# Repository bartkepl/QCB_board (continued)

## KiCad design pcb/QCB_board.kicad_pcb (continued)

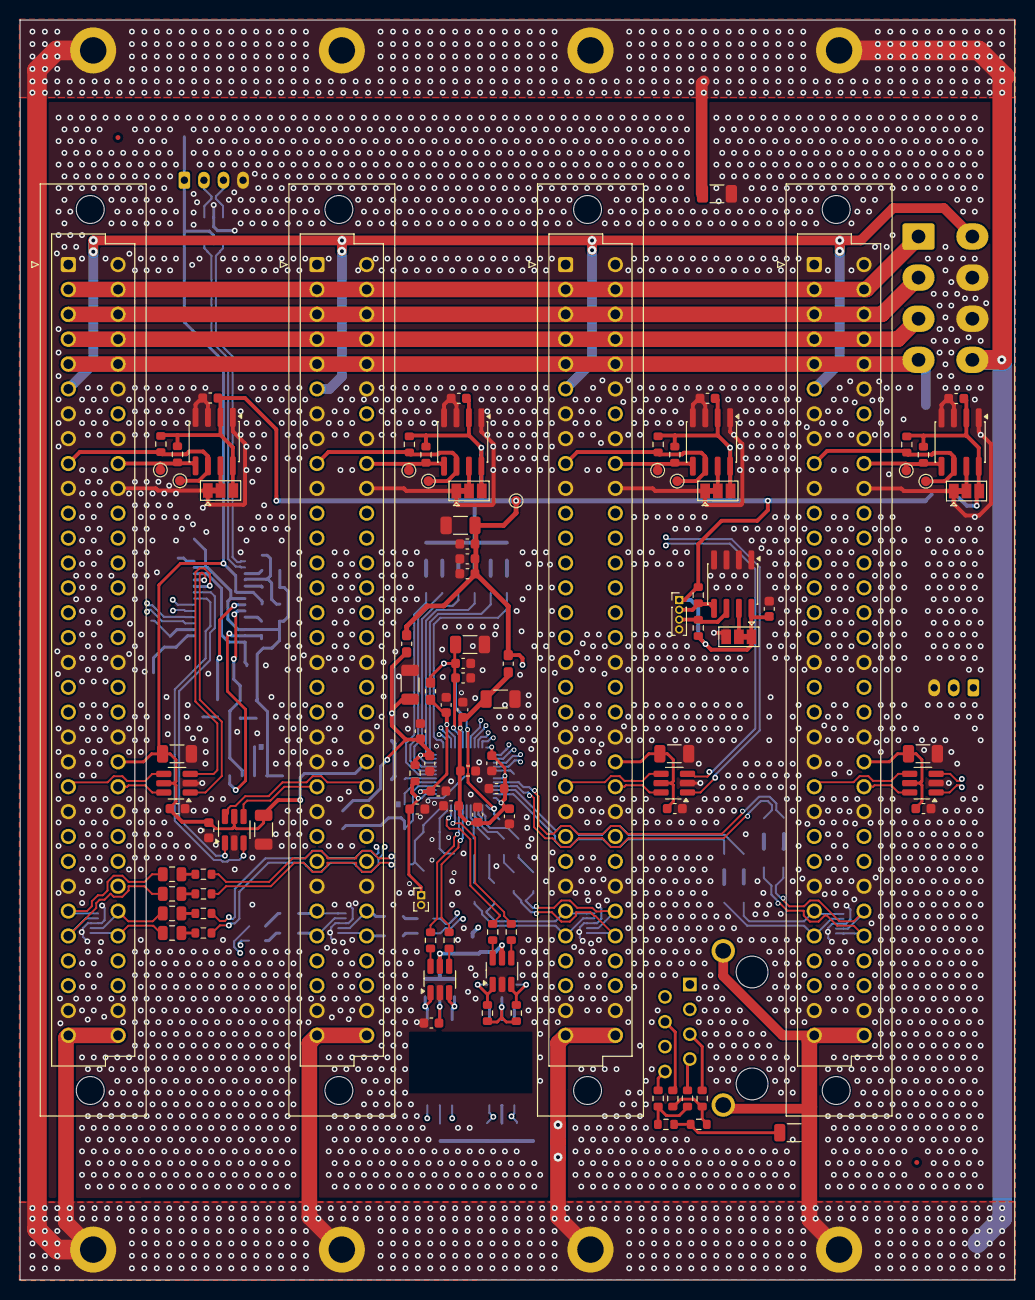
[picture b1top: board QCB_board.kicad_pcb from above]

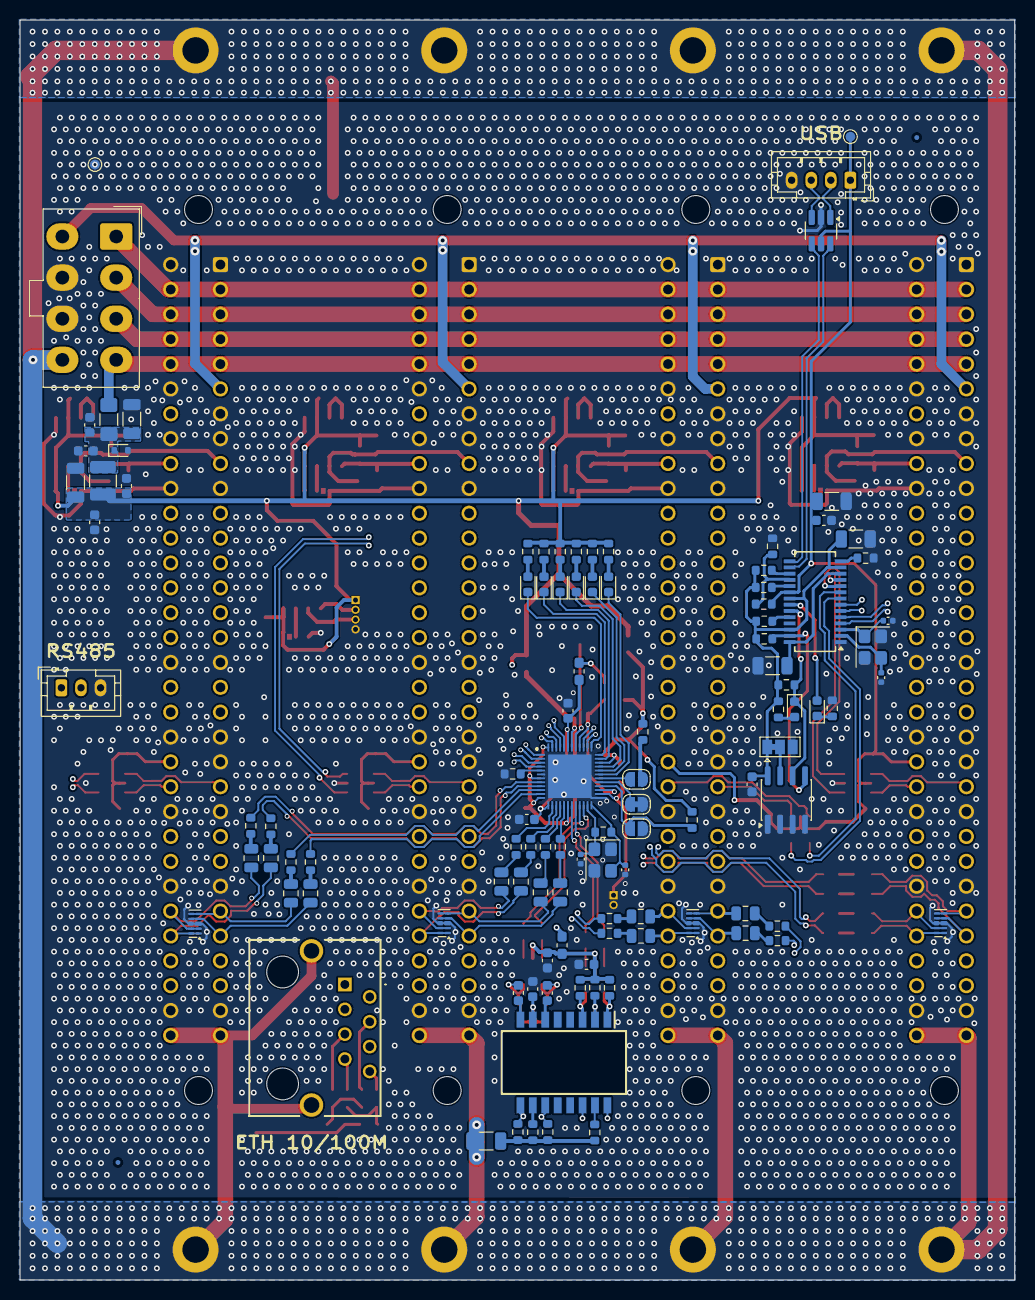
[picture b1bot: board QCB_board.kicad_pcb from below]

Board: 4 copper layers, 101.6 x 128.7 mm, 222 parts (110 on the bottom side), 166 nets.

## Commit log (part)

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2026-05-18 Schematic design
2026-05-18 More schematic
2026-05-19 Add symbols and adjust component positions in eth_switch schematic
2026-06-29 Sch complete, starting pcb
2026-06-30 Routing
